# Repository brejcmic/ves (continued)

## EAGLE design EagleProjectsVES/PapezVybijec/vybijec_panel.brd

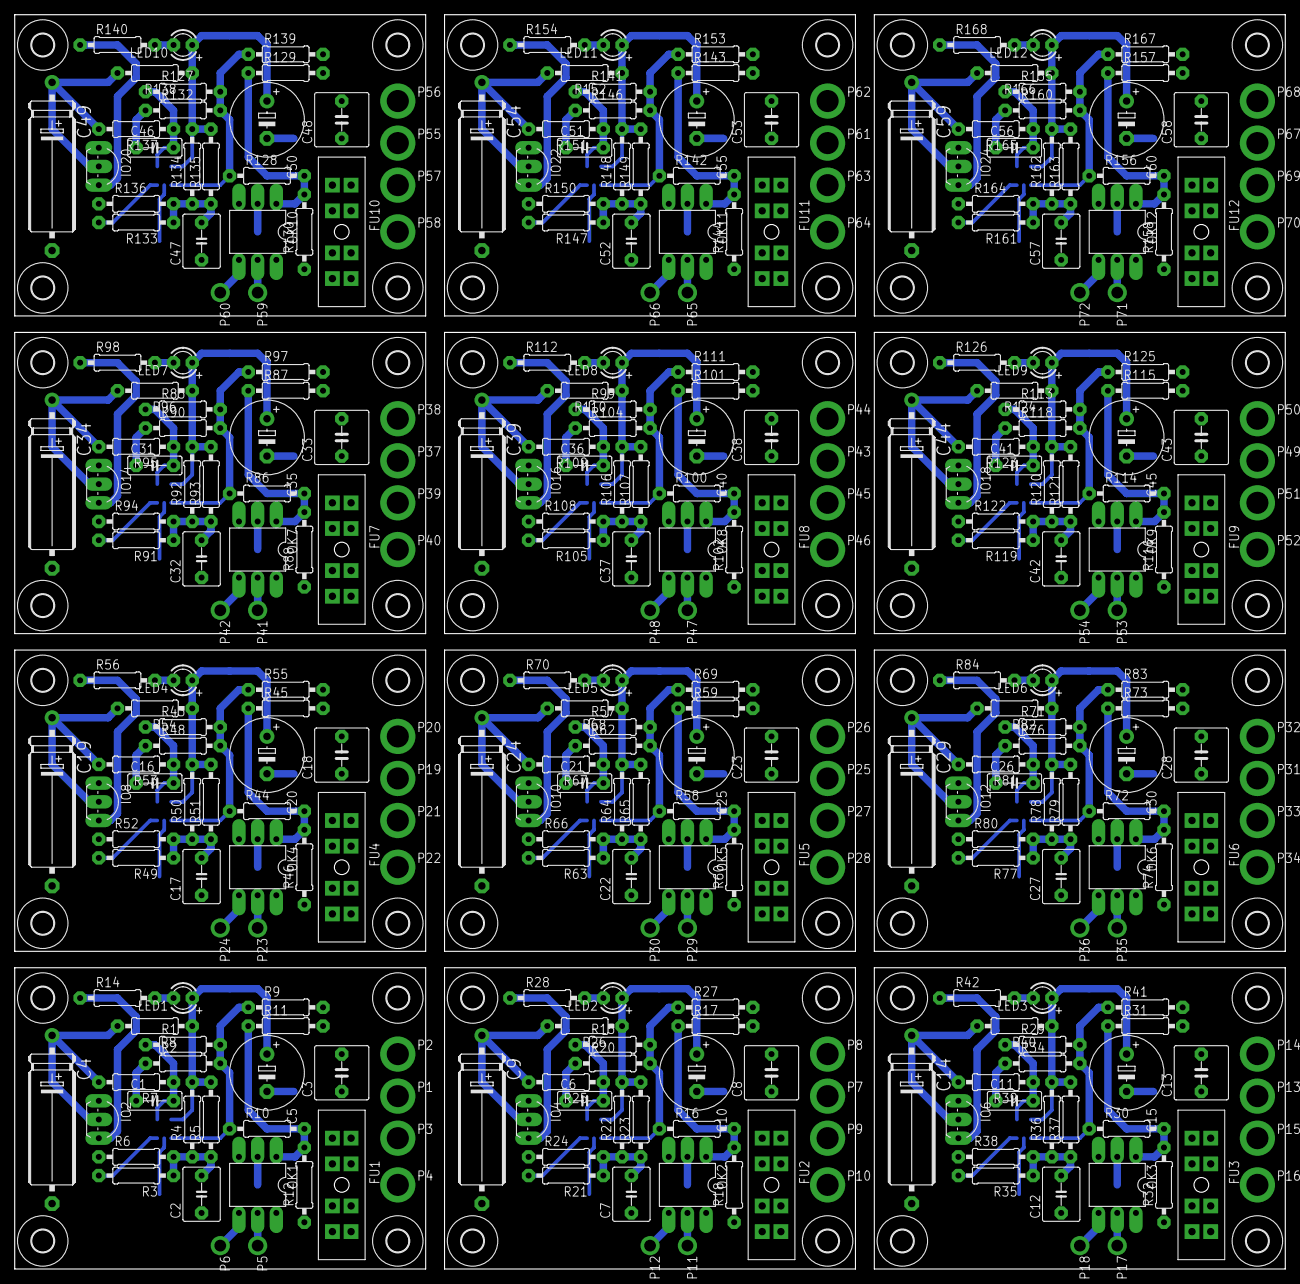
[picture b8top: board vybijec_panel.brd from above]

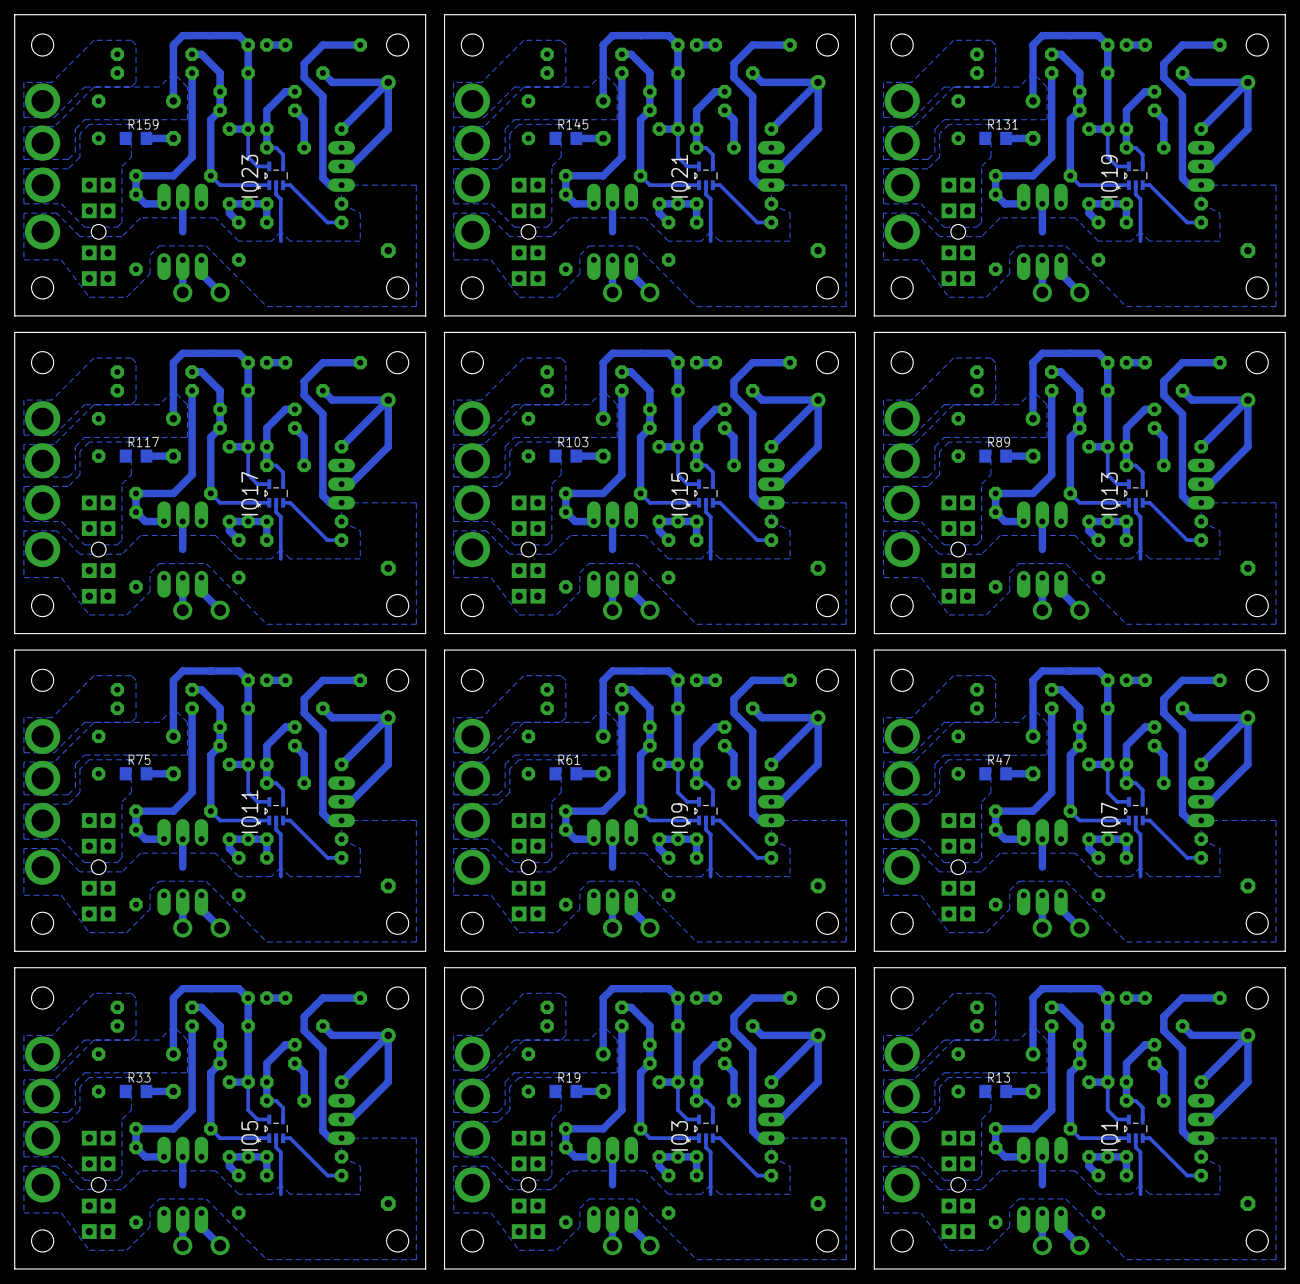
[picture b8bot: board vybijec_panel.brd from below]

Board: 2 copper layers, 172.7 x 170.5 mm, 408 parts (24 on the bottom side), 180 nets.

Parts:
C1, C6, C11, C16, C21, C26, C31, C36, C41, C46, C51, C56: 100k; C050-025X075
C2, C7, C12, C17, C22, C27, C32, C37, C42, C47, C52, C57: 2M2; C050-050X075
C3, C8, C13, C18, C23, C28, C33, C38, C43, C48, C53, C58: 15M; C050-075X075
C4, C9, C14, C19, C24, C29, C34, C39, C44, C49, C54, C59: 20M; E22-6
C5, C10, C15, C20, C25, C30, C35, C40, C45, C50, C55, C60: 2G2; E5-10,5
FU1, FU2, FU3, FU4, FU5, FU6, FU7, FU8, FU9, FU10, FU11, FU12: 20A; POJ20X6
IO1, IO3, IO5, IO7, IO9, IO11, IO13, IO15, IO17, IO19, IO21, IO23: NCS2001SN2T1G; SOT95P275X110-5N
IO2, IO4, IO6, IO8, IO10, IO12, IO14, IO16, IO18, IO20, IO22, IO24: LM285Z-2V5; TO92-
LED1, LED2, LED3, LED4, LED5, LED6, LED7, LED8, LED9, LED10, LED11, LED12: LED3MM
OK1, OK2, OK3, OK4, OK5, OK6, OK7, OK8, OK9, OK10, OK11, OK12: 4N35; DIL06
P1, P7, P13, P19, P25, P31, P37, P43, P49, P55, P61, P67: COLLECTOR; PAD3MM
P2, P8, P14, P20, P26, P32, P38, P44, P50, P56, P62, P68: BASE; PAD3MM
P3, P9, P15, P21, P27, P33, P39, P45, P51, P57, P63, P69: EMITTER; PAD3MM
P4, P10, P16, P22, P28, P34, P40, P46, P52, P58, P64, P70: GROUND; PAD3MM
P5, P11, P17, P23, P29, P35, P41, P47, P53, P59, P65, P71: COL; PAD1.6MM
P6, P12, P18, P24, P30, P36, P42, P48, P54, P60, P66, P72: EMIT; PAD1.6MM
R1, R15, R29, R43, R57, R71, R85, R99, R113, R127, R141, R155: M33; 0207/10
R2, R10, R16, R20, R30, R34, R44, R48, R58, R62, R72, R76, R86, R90, R100, R104, R114, R118, R128, R132, R142, R146, R156, R160: 15k; 0207/10
R3, R21, R35, R49, R63, R77, R91, R105, R119, R133, R147, R161: 1k2; 0207/10
R4, R22, R36, R50, R64, R78, R92, R106, R120, R134, R148, R162: 3M3; 0207/10
R5, R7, R23, R25, R37, R39, R51, R53, R65, R67, R79, R81, R93, R95, R107, R109, R121, R123, R135, R137, R149, R151, R163, R165: 3k3; 0207/10
R6, R12, R18, R24, R32, R38, R46, R52, R60, R66, R74, R80, R88, R94, R102, R108, R116, R122, R130, R136, R144, R150, R158, R164: 5k6; 0207/10
R8, R26, R40, R54, R68, R82, R96, R110, R124, R138, R152, R166: 12k; 0207/10
R9, R27, R41, R55, R69, R83, R97, R111, R125, R139, R153, R167: 120R; 0207/10
R11, R17, R31, R45, R59, R73, R87, R101, R115, R129, R143, R157: 2k2; 0207/10
R13, R19, R33, R47, R61, R75, R89, R103, R117, R131, R145, R159: 1R0; R1206
R14, R28, R42, R56, R70, R84, R98, R112, R126, R140, R154, R168: 330R; 0207/10
U$1, U$2, U$3, U$4, U$5, U$6, U$7, U$8, U$9, U$10, U$11, U$12, U$13, U$14, U$15, U$16, U$17, U$18, U$19, U$20, U$21, U$22, U$23, U$24, U$25, U$26, U$27, U$28, U$29, U$30, U$31, U$32, U$33, U$34, U$35, U$36, U$37, U$38, U$39, U$40, U$41, U$42, U$43, U$44, U$45, U$46, U$47, U$48: 3,0

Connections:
GND: C2.1, C4.-, FU1.2-1, FU1.2-2, FU1.2-3, FU1.2-4, IO1.2, IO2.1, OK1.2, P4.1, R6.1, R12.1, R14.1
GND1: C7.1, C9.-, FU2.2-1, FU2.2-2, FU2.2-3, FU2.2-4, IO3.2, IO4.1, OK2.2, P10.1, R18.1, R24.1, R28.1
GND2: C12.1, C14.-, FU3.2-1, FU3.2-2, FU3.2-3, FU3.2-4, IO5.2, IO6.1, OK3.2, P16.1, R32.1, R38.1, R42.1
GND3: C17.1, C19.-, FU4.2-1, FU4.2-2, FU4.2-3, FU4.2-4, IO7.2, IO8.1, OK4.2, P22.1, R46.1, R52.1, R56.1
GND4: C22.1, C24.-, FU5.2-1, FU5.2-2, FU5.2-3, FU5.2-4, IO9.2, IO10.1, OK5.2, P28.1, R60.1, R66.1, R70.1
GND5: C27.1, C29.-, FU6.2-1, FU6.2-2, FU6.2-3, FU6.2-4, IO11.2, IO12.1, OK6.2, P34.1, R74.1, R80.1, R84.1
GND6: C32.1, C34.-, FU7.2-1, FU7.2-2, FU7.2-3, FU7.2-4, IO13.2, IO14.1, OK7.2, P40.1, R88.1, R94.1, R98.1
GND7: C37.1, C39.-, FU8.2-1, FU8.2-2, FU8.2-3, FU8.2-4, IO15.2, IO16.1, OK8.2, P46.1, R102.1, R108.1, R112.1
GND8: C42.1, C44.-, FU9.2-1, FU9.2-2, FU9.2-3, FU9.2-4, IO17.2, IO18.1, OK9.2, P52.1, R116.1, R122.1, R126.1
GND9: C47.1, C49.-, FU10.2-1, FU10.2-2, FU10.2-3, FU10.2-4, IO19.2, IO20.1, OK10.2, P58.1, R130.1, R136.1, R140.1
GND10: C52.1, C54.-, FU11.2-1, FU11.2-2, FU11.2-3, FU11.2-4, IO21.2, IO22.1, OK11.2, P64.1, R144.1, R150.1, R154.1
GND11: C57.1, C59.-, FU12.2-1, FU12.2-2, FU12.2-3, FU12.2-4, IO23.2, IO24.1, OK12.2, P70.1, R158.1, R164.1, R168.1
unnamed: C1.1, R2.1
unnamed: IO1.1, R1.2, R2.2, R9.1, R10.1
unnamed: C4.+, IO2.2, R7.2, R8.2
unnamed: C1.2, IO1.4, R1.1, R7.1
unnamed: IO1.3, R3.2
unnamed: C2.2, R3.1, R4.1, R5.1, R6.2
unnamed: C3.1, FU1.1-1, FU1.1-2, FU1.1-3, FU1.1-4, P3.1, R13.1
unnamed: OK1.1, R10.2, R11.1, R12.2
unnamed: P2.1, R9.2, R11.2
unnamed: OK1.5, P5.P$1
unnamed: OK1.4, P6.P$1
unnamed: LED1.K, R14.2
unnamed: IO3.1, R15.2, R16.1, R20.2, R27.1
unnamed: C5.-, R13.2
unnamed: C6.2, IO3.4, R15.1, R25.1
unnamed: IO3.3, R21.2
unnamed: C7.2, R21.1, R22.1, R23.1, R24.2
unnamed: C9.+, IO4.2, R25.2, R26.2
unnamed: OK2.1, R16.2, R17.1, R18.2
unnamed: P8.1, R17.2, R27.2
unnamed: OK2.5, P11.P$1
unnamed: OK2.4, P12.P$1
unnamed: C10.-, R19.2
unnamed: C8.1, FU2.1-1, FU2.1-2, FU2.1-3, FU2.1-4, P9.1, R19.1
unnamed: C6.1, R20.1
unnamed: LED2.K, R28.2
unnamed: IO5.1, R29.2, R30.1, R34.2, R41.1
unnamed: C11.2, IO5.4, R29.1, R39.1
unnamed: IO5.3, R35.2
unnamed: C12.2, R35.1, R36.1, R37.1, R38.2
unnamed: C14.+, IO6.2, R39.2, R40.2
unnamed: OK3.1, R30.2, R31.1, R32.2
unnamed: P14.1, R31.2, R41.2
unnamed: OK3.5, P17.P$1
unnamed: OK3.4, P18.P$1
unnamed: C15.-, R33.2
unnamed: C13.1, FU3.1-1, FU3.1-2, FU3.1-3, FU3.1-4, P15.1, R33.1
unnamed: C11.1, R34.1
unnamed: LED3.K, R42.2
unnamed: IO7.1, R43.2, R44.1, R48.2, R55.1
unnamed: C16.2, IO7.4, R43.1, R53.1
unnamed: IO7.3, R49.2
unnamed: C17.2, R49.1, R50.1, R51.1, R52.2
unnamed: C19.+, IO8.2, R53.2, R54.2
unnamed: OK4.1, R44.2, R45.1, R46.2
unnamed: P20.1, R45.2, R55.2
unnamed: OK4.5, P23.P$1
unnamed: OK4.4, P24.P$1
unnamed: C20.-, R47.2
unnamed: C18.1, FU4.1-1, FU4.1-2, FU4.1-3, FU4.1-4, P21.1, R47.1
unnamed: C16.1, R48.1
unnamed: LED4.K, R56.2
unnamed: IO9.1, R57.2, R58.1, R62.2, R69.1
unnamed: C21.2, IO9.4, R57.1, R67.1
unnamed: IO9.3, R63.2
unnamed: C22.2, R63.1, R64.1, R65.1, R66.2
unnamed: C24.+, IO10.2, R67.2, R68.2
unnamed: OK5.1, R58.2, R59.1, R60.2
unnamed: P26.1, R59.2, R69.2
unnamed: OK5.5, P29.P$1
unnamed: OK5.4, P30.P$1
unnamed: C25.-, R61.2
unnamed: C23.1, FU5.1-1, FU5.1-2, FU5.1-3, FU5.1-4, P27.1, R61.1
unnamed: C21.1, R62.1
unnamed: LED5.K, R70.2
unnamed: IO11.1, R71.2, R72.1, R76.2, R83.1
unnamed: C26.2, IO11.4, R71.1, R81.1
unnamed: IO11.3, R77.2
unnamed: C27.2, R77.1, R78.1, R79.1, R80.2
unnamed: C29.+, IO12.2, R81.2, R82.2
unnamed: OK6.1, R72.2, R73.1, R74.2
unnamed: P32.1, R73.2, R83.2
unnamed: OK6.5, P35.P$1
unnamed: OK6.4, P36.P$1
unnamed: C30.-, R75.2
unnamed: C28.1, FU6.1-1, FU6.1-2, FU6.1-3, FU6.1-4, P33.1, R75.1
unnamed: C26.1, R76.1
unnamed: LED6.K, R84.2
unnamed: IO13.1, R85.2, R86.1, R90.2, R97.1
unnamed: C31.2, IO13.4, R85.1, R95.1
unnamed: IO13.3, R91.2
unnamed: C32.2, R91.1, R92.1, R93.1, R94.2
unnamed: C34.+, IO14.2, R95.2, R96.2
unnamed: OK7.1, R86.2, R87.1, R88.2
unnamed: P38.1, R87.2, R97.2
unnamed: OK7.5, P41.P$1
unnamed: OK7.4, P42.P$1
unnamed: C35.-, R89.2
unnamed: C33.1, FU7.1-1, FU7.1-2, FU7.1-3, FU7.1-4, P39.1, R89.1
unnamed: C31.1, R90.1
unnamed: LED7.K, R98.2
unnamed: IO15.1, R99.2, R100.1, R104.2, R111.1
unnamed: C36.2, IO15.4, R99.1, R109.1
unnamed: IO15.3, R105.2
unnamed: C37.2, R105.1, R106.1, R107.1, R108.2
unnamed: C39.+, IO16.2, R109.2, R110.2
unnamed: OK8.1, R100.2, R101.1, R102.2
unnamed: P44.1, R101.2, R111.2
unnamed: OK8.5, P47.P$1
unnamed: OK8.4, P48.P$1
unnamed: C40.-, R103.2
unnamed: C38.1, FU8.1-1, FU8.1-2, FU8.1-3, FU8.1-4, P45.1, R103.1
unnamed: C36.1, R104.1
unnamed: LED8.K, R112.2
unnamed: IO17.1, R113.2, R114.1, R118.2, R125.1
unnamed: C41.2, IO17.4, R113.1, R123.1
unnamed: IO17.3, R119.2
unnamed: C42.2, R119.1, R120.1, R121.1, R122.2
unnamed: C44.+, IO18.2, R123.2, R124.2
unnamed: OK9.1, R114.2, R115.1, R116.2
unnamed: P50.1, R115.2, R125.2
unnamed: OK9.5, P53.P$1
unnamed: OK9.4, P54.P$1
unnamed: C45.-, R117.2
unnamed: C43.1, FU9.1-1, FU9.1-2, FU9.1-3, FU9.1-4, P51.1, R117.1
unnamed: C41.1, R118.1
unnamed: LED9.K, R126.2
unnamed: IO19.1, R127.2, R128.1, R132.2, R139.1
unnamed: C46.2, IO19.4, R127.1, R137.1
unnamed: IO19.3, R133.2
unnamed: C47.2, R133.1, R134.1, R135.1, R136.2
unnamed: C49.+, IO20.2, R137.2, R138.2
unnamed: OK10.1, R128.2, R129.1, R130.2
unnamed: P56.1, R129.2, R139.2
unnamed: OK10.5, P59.P$1
unnamed: OK10.4, P60.P$1
unnamed: C50.-, R131.2
unnamed: C48.1, FU10.1-1, FU10.1-2, FU10.1-3, FU10.1-4, P57.1, R131.1
unnamed: C46.1, R132.1
unnamed: LED10.K, R140.2
unnamed: IO21.1, R141.2, R142.1, R146.2, R153.1
unnamed: C51.2, IO21.4, R141.1, R151.1
unnamed: IO21.3, R147.2
unnamed: C52.2, R147.1, R148.1, R149.1, R150.2
unnamed: C54.+, IO22.2, R151.2, R152.2
unnamed: OK11.1, R142.2, R143.1, R144.2
unnamed: P62.1, R143.2, R153.2
unnamed: OK11.5, P65.P$1
unnamed: OK11.4, P66.P$1
unnamed: C55.-, R145.2
unnamed: C53.1, FU11.1-1, FU11.1-2, FU11.1-3, FU11.1-4, P63.1, R145.1
unnamed: C51.1, R146.1
unnamed: LED11.K, R154.2
unnamed: IO23.1, R155.2, R156.1, R160.2, R167.1
unnamed: C56.2, IO23.4, R155.1, R165.1
unnamed: IO23.3, R161.2
unnamed: C57.2, R161.1, R162.1, R163.1, R164.2
unnamed: C59.+, IO24.2, R165.2, R166.2
unnamed: OK12.1, R156.2, R157.1, R158.2
unnamed: P68.1, R157.2, R167.2
unnamed: OK12.5, P71.P$1
unnamed: OK12.4, P72.P$1
unnamed: C60.-, R159.2
unnamed: C58.1, FU12.1-1, FU12.1-2, FU12.1-3, FU12.1-4, P69.1, R159.1
unnamed: C56.1, R160.1
unnamed: LED12.K, R168.2
VCC: C3.2, C5.+, IO1.5, LED1.A, P1.1, R4.2, R5.2, R8.1
VCC1: C8.2, C10.+, IO3.5, LED2.A, P7.1, R22.2, R23.2, R26.1
VCC2: C13.2, C15.+, IO5.5, LED3.A, P13.1, R36.2, R37.2, R40.1
VCC3: C18.2, C20.+, IO7.5, LED4.A, P19.1, R50.2, R51.2, R54.1
VCC4: C23.2, C25.+, IO9.5, LED5.A, P25.1, R64.2, R65.2, R68.1
VCC5: C28.2, C30.+, IO11.5, LED6.A, P31.1, R78.2, R79.2, R82.1
VCC6: C33.2, C35.+, IO13.5, LED7.A, P37.1, R92.2, R93.2, R96.1
VCC7: C38.2, C40.+, IO15.5, LED8.A, P43.1, R106.2, R107.2, R110.1
VCC8: C43.2, C45.+, IO17.5, LED9.A, P49.1, R120.2, R121.2, R124.1
VCC9: C48.2, C50.+, IO19.5, LED10.A, P55.1, R134.2, R135.2, R138.1
VCC10: C53.2, C55.+, IO21.5, LED11.A, P61.1, R148.2, R149.2, R152.1
VCC11: C58.2, C60.+, IO23.5, LED12.A, P67.1, R162.2, R163.2, R166.1

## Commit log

2015-10-02 prvni commit
2015-10-02 Hotove navody na nelinearni rezistory, feroelektricke kondenzatory a vysokofrekvencni civky.
2015-10-02 Hotovy navod na pajeni a mereni rc nad 1MHz.
2015-10-04 Doplneny podklady pro zbyvajici navody. Zadny neni hotovy.
2015-10-09 Navody byly rozdeleny do vice stranek.
2015-10-12 Doplneny obrazky k jednotlivym uloham.
2015-10-14 První tři úlohy jsou plně popsány, pájení se popisovat víc nebude. Je třeba dodělat polovodiče a fotovoltaické panely.
2015-10-15 Hotovy navod na cvika rc do 1 MHz.
2015-10-16 Hotovy navod pro mereni RC nad 1 MHz
2015-10-19 Hotovy navod na polovodice
2015-10-19 Hotove nelinearni rezistory
2015-10-19 Hotove vf civky
2015-10-19 Vsechny navody vystaveny na moodle. Chybi fotovoltaicke panely.
2015-10-20 Hotove vsechny navody, predano na moodle.
2015-11-06 Opraveny chyby v zadani navodu - predevsim polovodice Nakresleni popisku pro pripravky měreni tranzistoru a zesilovac
2015-11-13 popisky k pripravkum
2016-01-21 Vf zesilovac pro Papeze v KiCad
2016-01-21 v gitignore doplneny soubory pro KiCad
2016-01-21 Opraveny chyby v navodu a vyplnovaci listek pro testy v Edubasi
2016-01-26 Finalni verze RF zesilovace pred vyrobou. Upraveny dleky privodu, popisy a velikosti plosek.
2016-02-02 DPS zesilovac: -upraveny diry na 0,8 mm pro kohouta a zvetseny centrealni a zemnici otvory pro privod kabelu.
2016-02-18 Zesilova-Papez: - vytvoreny podklady pro osazovani
2016-02-24 Zesilovac Papez: - uprava potisku BNC pro vyrobu v Cine nebo Pragoboardu - vygenerovani gerber dat
2016-10-03 Uprava poradi uloh a zakladni schema pripravku pro mereni diod a tranzistoru.
2016-10-04 Dotvorene schema mereni tranzistoru - nutno predelat pripojne body meraku a zdroju na svorkovnice ARK
2016-10-04 Predelany svorkovnice
2016-10-05 Navrzena DPS pro mereni tranzistoru. Vyroba musi byt v Pragoboardu.
2016-10-19 Tranzistory predany k vyrobe
2016-11-02 Uprava zadani el. obvodu a polovodicu.
2016-11-02 DPS Tranzistory: - opraveny chyby v desce, nyni by mela byt pouzitelna az do 30 V UCE
2016-11-15 DPS Tranzisotry: - snizeno zesileni zpetne vazby - pridan odpor ke kondenzatoru sample-hold tak, aby vytvoril integracni clanek.
2016-11-24 Nova verze piskace pro pajeni
2016-12-01 Nova verze DPS pro pajeni
2016-12-01 Uprava navodu - nove vzorky a pajeni
2016-12-01 Uprava vyplnovaciho listku pro pololetni test
2017-06-13 PapezVybijec: -schema a zakladni rozmisteni soucastek
2017-06-13 PapezVybijec: - hotova dps
2017-06-13 PapezVybijec: - nahledy dps pro prvni kontrolu
2017-06-14 testy: - vyplnovaci listky
2017-06-14 gitignore: - pridany knihovny
2017-06-14 PapezVybijec: - pridany knihovny
2017-06-14 PapezVybijec: - opraveny rozmery nytu
2017-06-14 PapezVybijec: - hotove podklady, - pridany navrhove pravidla
2017-09-20 Eagle: - vybijec pro Papeze - tranzistory pred odeslanim do pragoboardu - navrh zdroju proudu
2017-09-22 Priprava pro semestr 2017-2018
2017-09-22 Novy popisek pro pripravek
2017-09-25 Tranzistory: Pravidla
2017-09-25 Tranzistory: pridana objednavka
2017-09-25 Doplneny chybejici soubory GERBER
2017-09-26 Tranzistory: - opravena dalsi chybka v napojeni emitoru a serioveho rezistoru
2017-10-10 PrednaskyEN: 1. prednaska, cast nazvoslovi, cast zakladni soucastky hotovo
2017-10-11 PrednaskaEN: hotovo pr1 - hotova prednaska na prvni hodinu
2017-10-26 Pridany anglicke prednasky - hotove P1-P3 x rozpracovana P4
2017-10-30 Oprava navodu cvik pro mereni nad 1MHz a pristroj Agilent E4991A
2017-10-31 Temer hotova anglicka prednaska 4 o kondenzatorech
2017-11-01 Hotova prednaska P4 o kondenzatorech
2017-11-02 Opravy v prednaskach a navodech na cviceni
2017-11-03 Priprava na prednasku 5
2017-11-09 Hotova prednaska P5 pro anglicany
2017-11-10 Oprava chyb v prednasce P5
2017-11-12 Rozpracovana verze prednasky P6 pro anglicany.
2017-11-13 U prednasky P6 upraven obr1 a pridelan prvni ukol mereni.
2017-11-14 Pridan slajd k P6
2017-11-15 Pridany testy Hajek
2017-11-15 Cast prednasky pro anglicany P6
2017-11-20 Prednaska P6 pro anglicany
2017-11-20 Projekt pro Papeze - bocnik k baterkam
2017-11-21 Hotovy vykonovy obvod simulujici zenerovu doidu
2017-11-21 Odstraneny nepotrebne soubory
2017-11-21 Zacatek prace na prednasce P7 pro anglicany
2017-11-21 Prednaska P7 pro anglicany ujasneny charakteristiky
2017-11-22 Hotovy panel pro Papezovu zenerku - zmensene prumery padu
2017-11-22 Hotova prednaska P7 pro anglicany
2017-11-23 Opraveny chyby v prednasce P7 pro anglicany
2017-11-28 Priprava na prednasku P8 pro anglicany
2017-11-28 Prednaska P8 pro anglicany - fotoodpory
2017-11-28 Prednaska P8 pro anglicany, pridana spousta obrazku
2017-11-29 Hotova prednaska P8 pro anglicany
2017-12-05 Priprava na prednasku P9 anglicani
2017-12-05 Pridany obrazky do prednasky P9 pro anglicany
2017-12-05 Pridelany dalsi obrazky do prednasky P9 pro anglicany.
2017-12-06 Hotova prednaska P9 pro anglicany
2017-12-13 Priprava prezentace P10 pro anglicany
2017-12-18 Hotova prednaska P10 pro anglicany.
2018-01-02 Pridany prednasky od Jirky Hajka
2018-01-02 Priprava prednasek P11 pro anglicany
2018-01-03 oprava prednasky P10 pro anglicany - stupne F na stupne C
2018-01-03 Hotova prednaska P11 pro anglicany
